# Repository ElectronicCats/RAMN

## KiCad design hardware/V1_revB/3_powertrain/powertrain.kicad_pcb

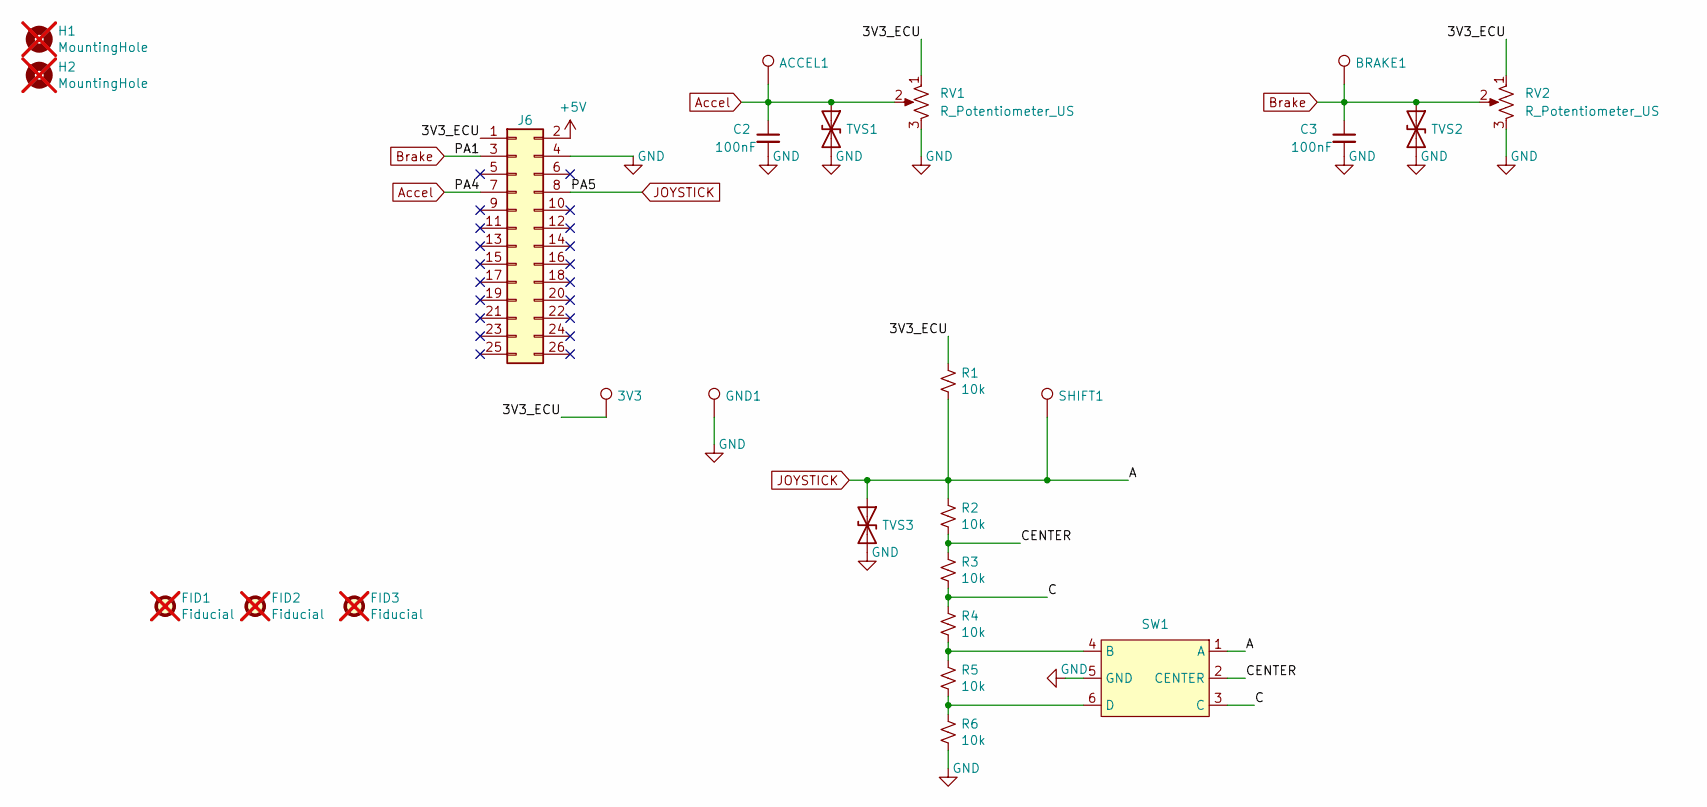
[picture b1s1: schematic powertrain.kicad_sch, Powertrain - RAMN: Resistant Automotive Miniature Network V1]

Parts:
3V3: TestPoint; KEYSTONE_5002; lcsc# C5277086
ACCEL1: TestPoint; KEYSTONE_5002; lcsc# C5277086
BRAKE1: TestPoint; KEYSTONE_5002; lcsc# C5277086
C2, C3: 100nF; C_0603_1608Metric; lcsc# C282519
FID1, FID2, FID3: Fiducial; Fiducial_1mm_Mask2mm; not fitted
GND1: TestPoint; KEYSTONE_5002; lcsc# C5277086
H1, H2: MountingHole; MountingHole_3.2mm_M3_ISO7380; not fitted
J6: PinSocket_2x13_P2.54mm_Vertical; lcsc# C2897414
R1, R2, R3, R4, R5, R6: 10k; R_0603_1608Metric; lcsc# C209220
RV1, RV2: R_Potentiometer_US; RS15111A900B; lcsc# C470417
SHIFT1: TestPoint; KEYSTONE_5002; lcsc# C5277086
SW1: SKRHADE010; lcsc# C202415
TVS1, TVS2, TVS3: D_TVS; D_SOD-123F; lcsc# C1849694

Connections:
+5V: J6.2
/3V3_ECU: 3V3.1 (1_1), J6.1, R1.1, RV1.1, RV2.1
/C: R3.2, R4.1, SW1.3 (C)
/CENTER: R2.2, R3.1, SW1.2 (CENTER)
Accel: ACCEL1.1 (1_1), C2.1, J6.7, RV1.2, TVS1.1 (A1)
Brake: BRAKE1.1 (1_1), C3.1, J6.3, RV2.2, TVS2.1 (A1)
GND: C2.2, C3.2, GND1.1 (1_1), J6.4, R6.2, RV1.3, RV2.3, SW1.5 (GND), TVS1.2 (A2), TVS2.2 (A2), TVS3.2 (A2)
JOYSTICK: J6.8, R1.2, R2.1, SHIFT1.1 (1_1), SW1.1 (A), TVS3.1 (A1)
unnamed: R4.2, R5.1, SW1.4 (B)
unnamed: R5.2, R6.1, SW1.6 (D)

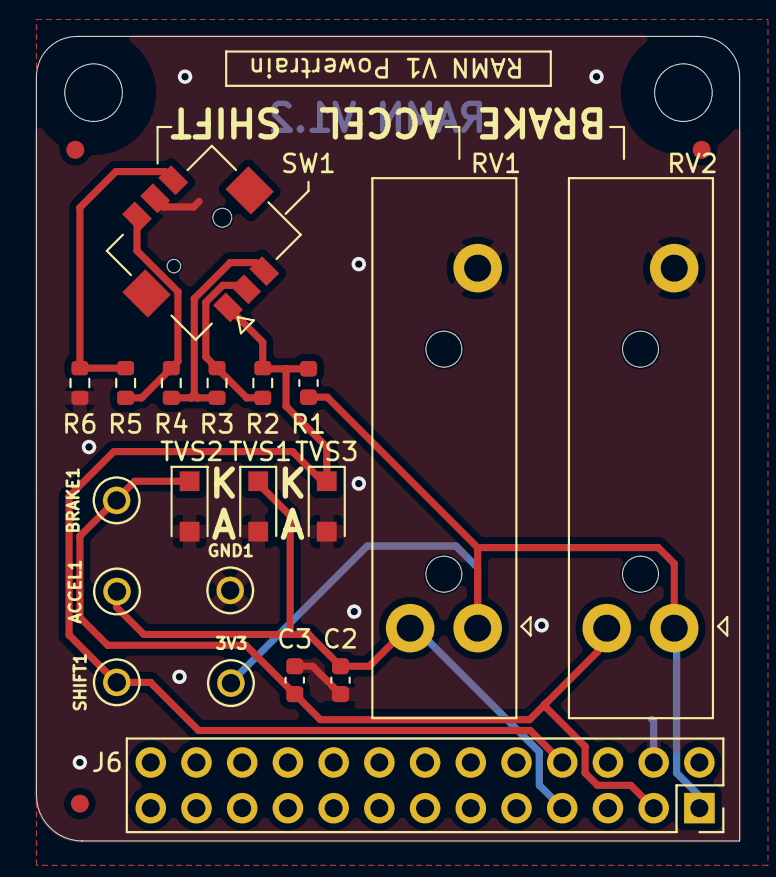
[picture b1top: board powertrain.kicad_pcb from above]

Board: 2 copper layers, 39.1 x 44.7 mm, 25 parts (0 on the bottom side), 9 nets.

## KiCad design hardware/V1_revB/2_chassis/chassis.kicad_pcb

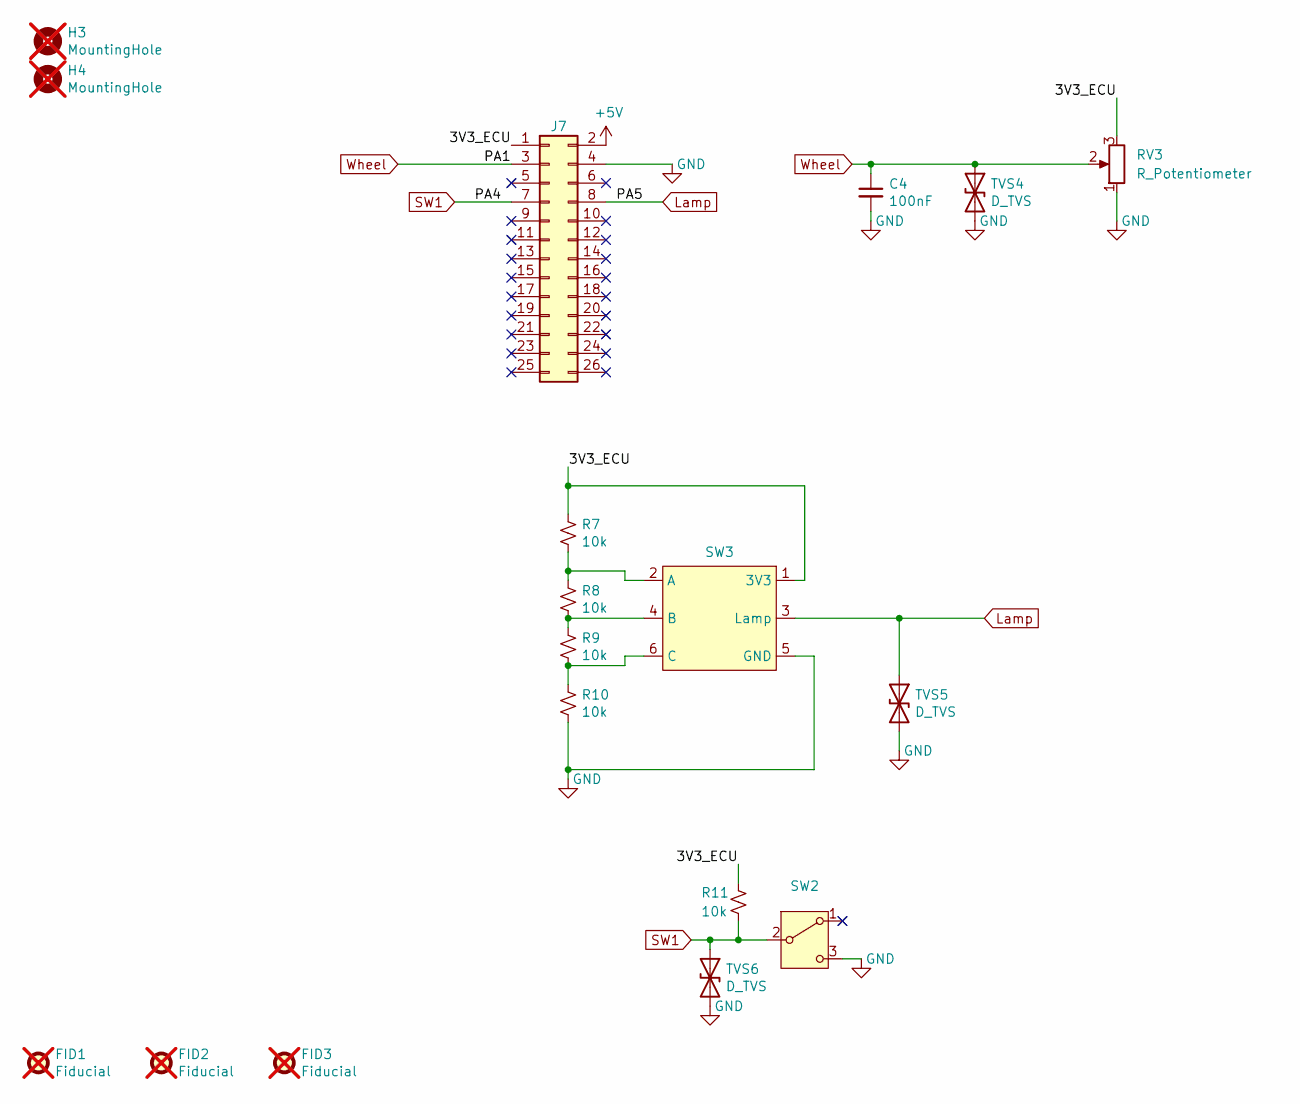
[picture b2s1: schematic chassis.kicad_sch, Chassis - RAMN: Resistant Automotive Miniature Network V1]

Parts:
C4: 100nF; C_0603_1608Metric; lcsc# C282519
FID1, FID2, FID3: Fiducial; Fiducial_1mm_Mask2mm; not fitted
H3, H4: MountingHole; MountingHole_3.2mm_M3_ISO7380; not fitted
J7: PinSocket_2x13_P2.54mm_Vertical; lcsc# C2897414
R7, R8, R9, R10, R11: 10k; R_0603_1608Metric; lcsc# C73809
RV3: R_Potentiometer; New_Pot; lcsc# C6139964
SW2: SW_CuK_OS102011MA1QN1_SPDT_Angled; lcsc# C226259
SW3: NR01; lcsc# C7250022
TVS4, TVS5, TVS6: D_TVS; D_SOD-123F; lcsc# C1849694

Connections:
+5V: J7.2
/3V3_ECU: J7.1, R7.1, R11.2, RV3.3, SW3.1 (3V3)
GND: C4.2, J7.4, R10.2, RV3.1, SW2.3 (C), SW3.5 (GND), TVS4.2 (A2), TVS5.2 (A2), TVS6.2 (A2)
Lamp: J7.8, SW3.3 (Lamp), TVS5.1 (A1)
unnamed: R7.2, R8.1, SW3.2 (A)
unnamed: R8.2, R9.1, SW3.4 (B)
unnamed: R9.2, R10.1, SW3.6 (C)
SW1: J7.7, R11.1, SW2.2 (B), TVS6.1 (A1)
Wheel: C4.1, J7.3, RV3.2, TVS4.1 (A1)

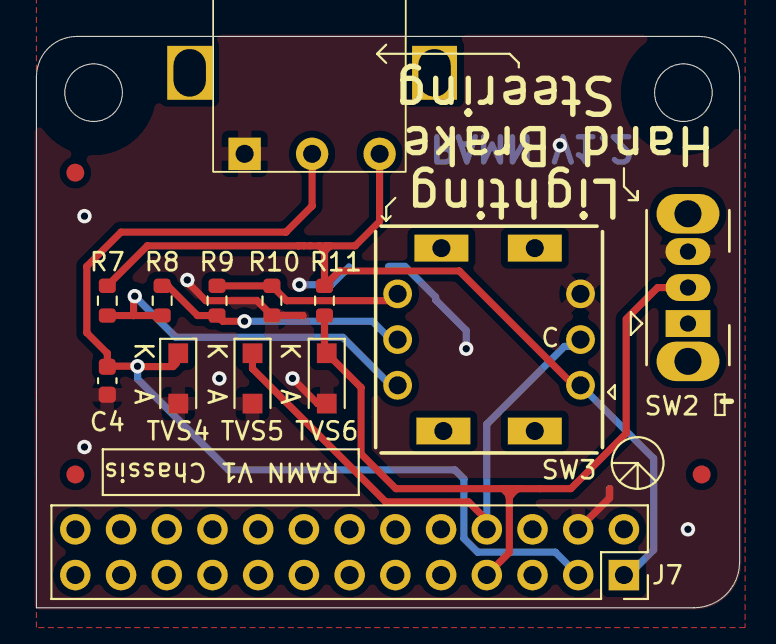
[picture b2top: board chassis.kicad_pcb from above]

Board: 2 copper layers, 39.1 x 31.7 mm, 18 parts (0 on the bottom side), 8 nets.

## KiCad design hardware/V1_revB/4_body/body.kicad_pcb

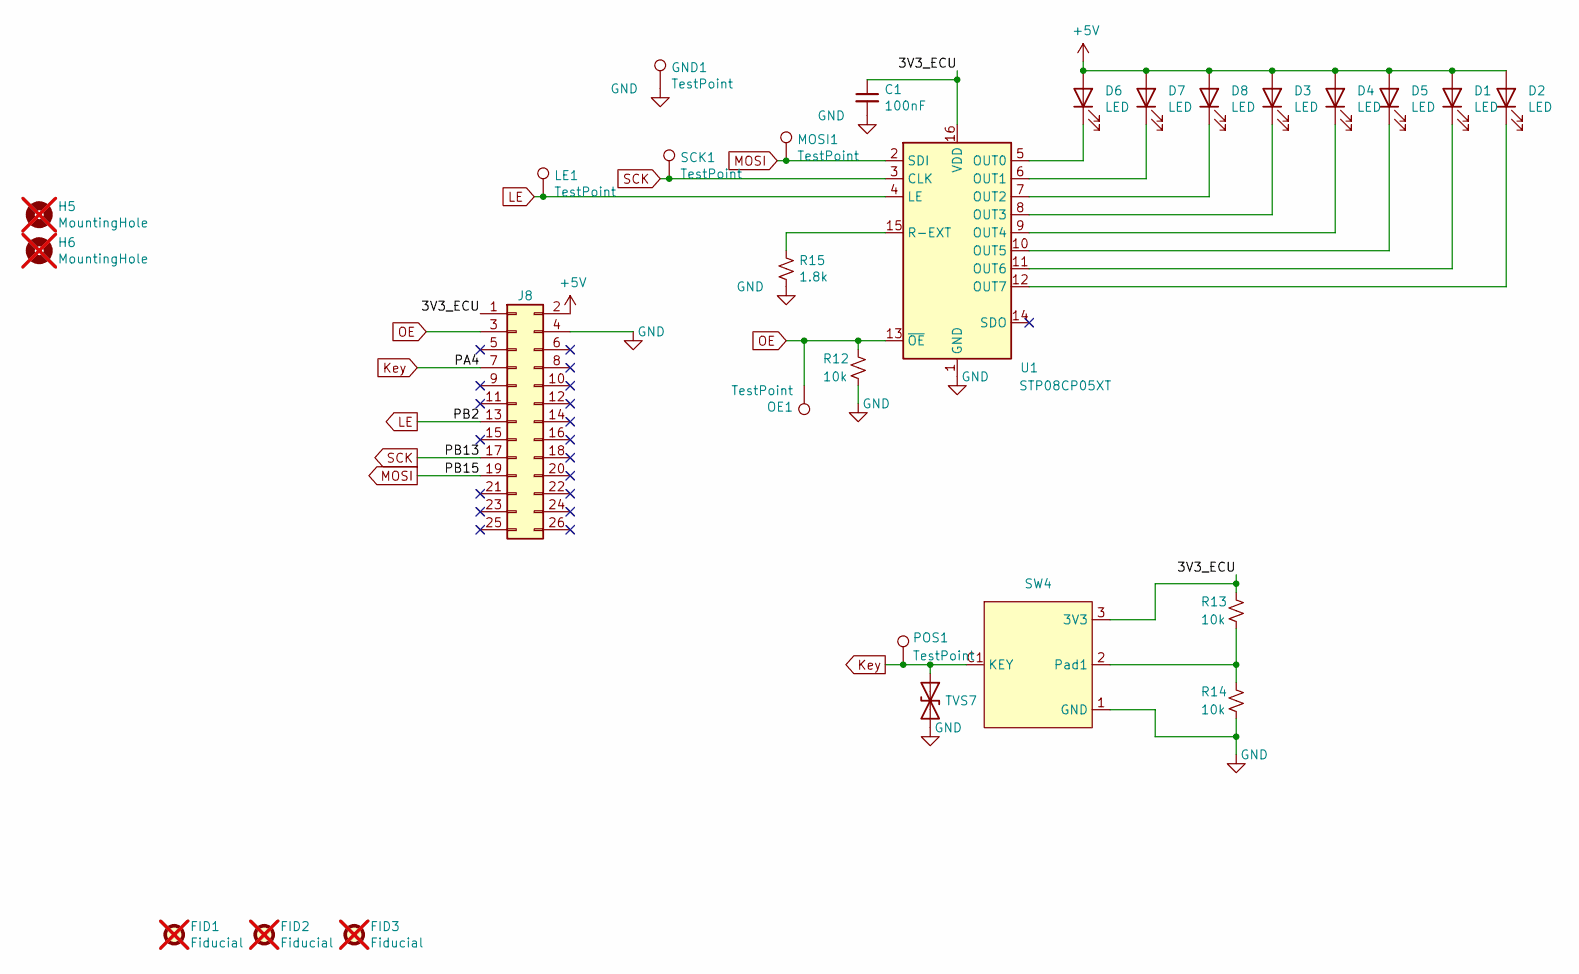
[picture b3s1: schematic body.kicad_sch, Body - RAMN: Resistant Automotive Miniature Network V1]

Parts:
C1: 100nF; C_0603_1608Metric; lcsc# C282519
D1, D2, D6: LED; LED_0603_1608Metric; lcsc# C51933295
D3, D4, D5: LED; LED_0603_1608Metric; lcsc# C510294
D7: LED; LED_0603_1608Metric; lcsc# C19273153
D8: LED; LED_0603_1608Metric; lcsc# C51933292
FID1, FID2, FID3: Fiducial; Fiducial_1mm_Mask2mm; not fitted
GND1: TestPoint; KEYSTONE_5002; lcsc# C5277086
H5, H6: MountingHole; MountingHole_3.2mm_M3_ISO7380; not fitted
J8: PinSocket_2x13_P2.54mm_Vertical; lcsc# C2897414
LE1: TestPoint; KEYSTONE_5002; lcsc# C5277086
MOSI1: TestPoint; KEYSTONE_5002; lcsc# C5277086
OE1: TestPoint; KEYSTONE_5002; lcsc# C5277086
POS1: TestPoint; KEYSTONE_5002; lcsc# C5277086
R12, R13, R14: 10k; R_0603_1608Metric; lcsc# C209220
R15: 1.8k; R_0603_1608Metric; lcsc# C171725
SCK1: TestPoint; KEYSTONE_5002; lcsc# C5277086
SW4: SK14dG13; lcsc# C34362858
TVS7: D_TVS; D_SOD-123F; lcsc# C1849694
U1: STP08CP05XT; HTSSOP-16-1EP_4.4x5mm_P0.65mm_EP3x3mm; lcsc# C2678539

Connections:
+5V: D1.2 (A), D2.2 (A), D3.2 (A), D4.2 (A), D5.2 (A), D6.2 (A), D7.2 (A), D8.2 (A), J8.2
/3V3_ECU: C1.1, J8.1, R13.2, SW4.3 (3V3), U1.16 (VDD)
GND: C1.2, GND1.1 (1_1), J8.4, R12.1, R14.1, R15.1, SW4.1 (GND), TVS7.2 (A2), U1.1 (GND), U1.17 (GND)
Key: J8.7, POS1.1 (1_1), SW4.C1 (KEY), TVS7.1 (A1)
LE: J8.13, LE1.1 (1_1), U1.4 (LE)
MOSI: J8.19, MOSI1.1 (1_1), U1.2 (SDI)
unnamed: D1.1 (K), U1.11 (OUT6)
unnamed: D2.1 (K), U1.12 (OUT7)
unnamed: D3.1 (K), U1.8 (OUT3)
unnamed: D4.1 (K), U1.9 (OUT4)
unnamed: D5.1 (K), U1.10 (OUT5)
unnamed: D6.1 (K), U1.5 (OUT0)
unnamed: D7.1 (K), U1.6 (OUT1)
unnamed: D8.1 (K), U1.7 (OUT2)
unnamed: R13.1, R14.2, SW4.2 (Pad1)
unnamed: R15.2, U1.15 (R-EXT)
OE: J8.3, OE1.1 (1_1), R12.2, U1.13 (~OE)
SCK: J8.17, SCK1.1 (1_1), U1.3 (CLK)

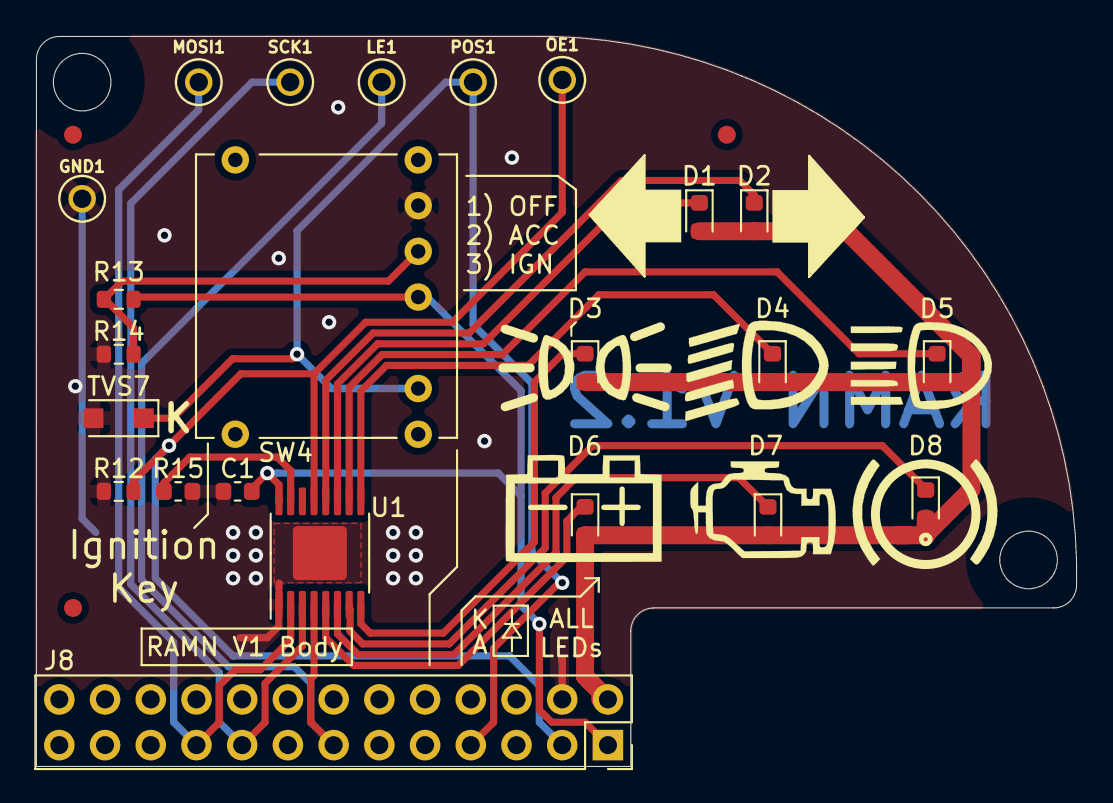
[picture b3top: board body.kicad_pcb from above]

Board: 2 copper layers, 57.8 x 40.6 mm, 28 parts (0 on the bottom side), 18 nets.

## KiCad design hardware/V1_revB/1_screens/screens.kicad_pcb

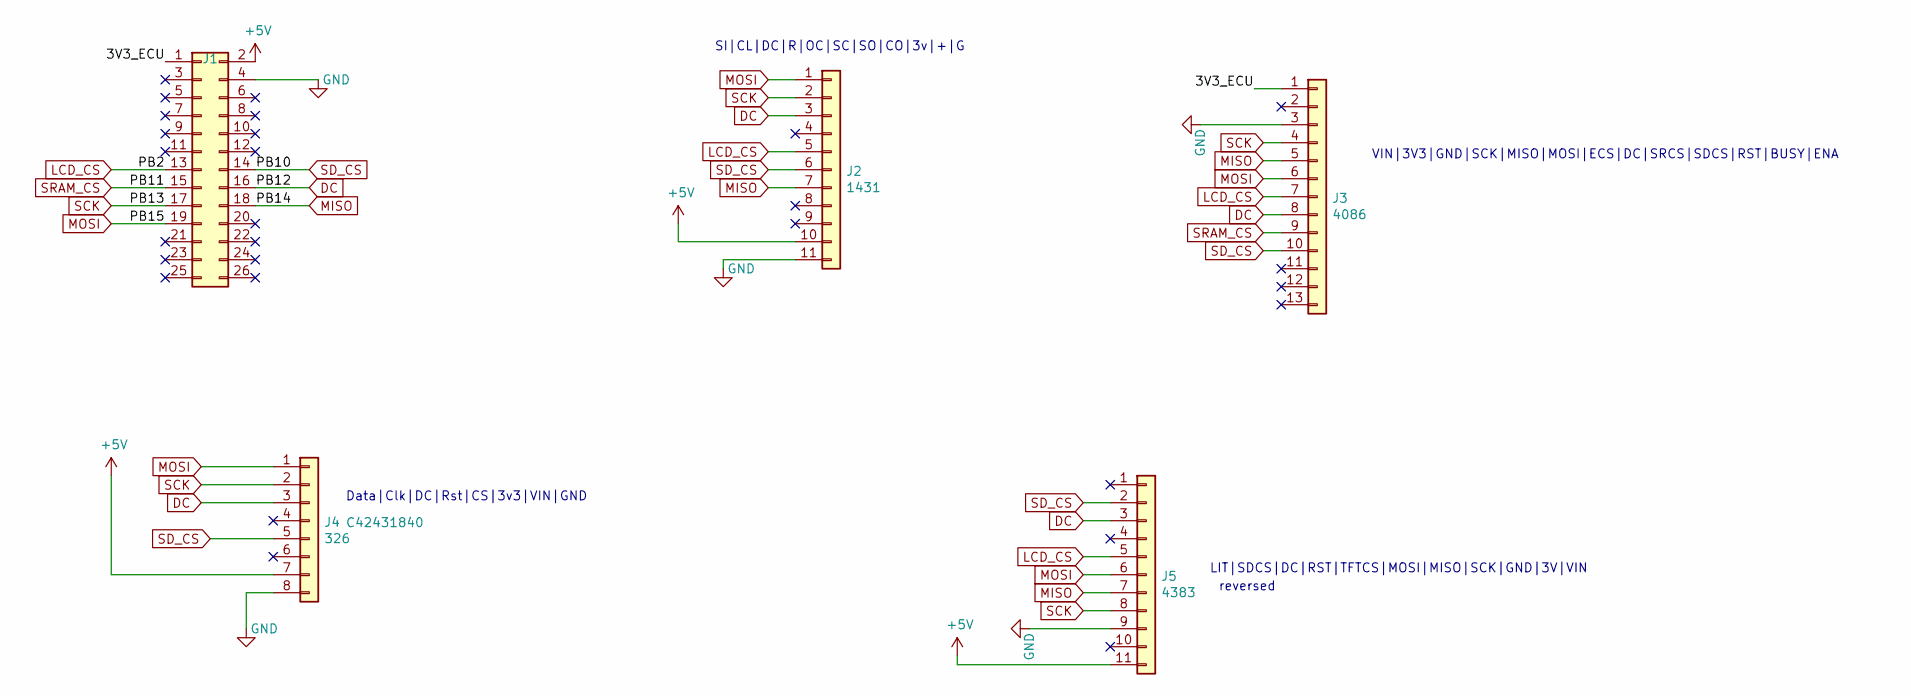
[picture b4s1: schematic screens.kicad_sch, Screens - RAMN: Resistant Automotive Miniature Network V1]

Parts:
J1: PinHeader_2x13_P2.54mm_Horizontal; LCSC C5412932
J2: 1431; PinSocket_1x11_P2.54mm_Vertical; LCSC C41417323
J3: 4086; PinSocket_1x13_P2.54mm_Vertical; LCSC C2905420
J4: 326; PinSocket_1x08_P2.54mm_Vertical; LCSC C42431840
J5: 4383; PinSocket_1x11_P2.54mm_Vertical; LCSC C41417323

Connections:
+5V: J1.2, J2.10, J4.7, J5.11
/3V3_ECU: J1.1, J3.1
DC: J1.16, J2.3, J3.8, J4.3, J5.3
GND: J1.4, J2.11, J3.3, J4.8, J5.9
LCD_CS: J1.13, J2.5, J3.7, J5.5
MISO: J1.18, J2.7, J3.5, J5.7
MOSI: J1.19, J2.1, J3.6, J4.1, J5.6
SCK: J1.17, J2.2, J3.4, J4.2, J5.8
SD_CS: J1.14, J2.6, J3.10, J4.5, J5.2
SRAM_CS: J1.15, J3.9

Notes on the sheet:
reversed
Data|Clk|DC|Rst|CS|3v3|VIN|GND
LIT|SDCS|DC|RST|TFTCS|MOSI|MISO|SCK|GND|3V|VIN
VIN|3V3|GND|SCK|MISO|MOSI|ECS|DC|SRCS|SDCS|RST|BUSY|ENA
SI|CL|DC|R|OC|SC|SO|CO|3v|+|G

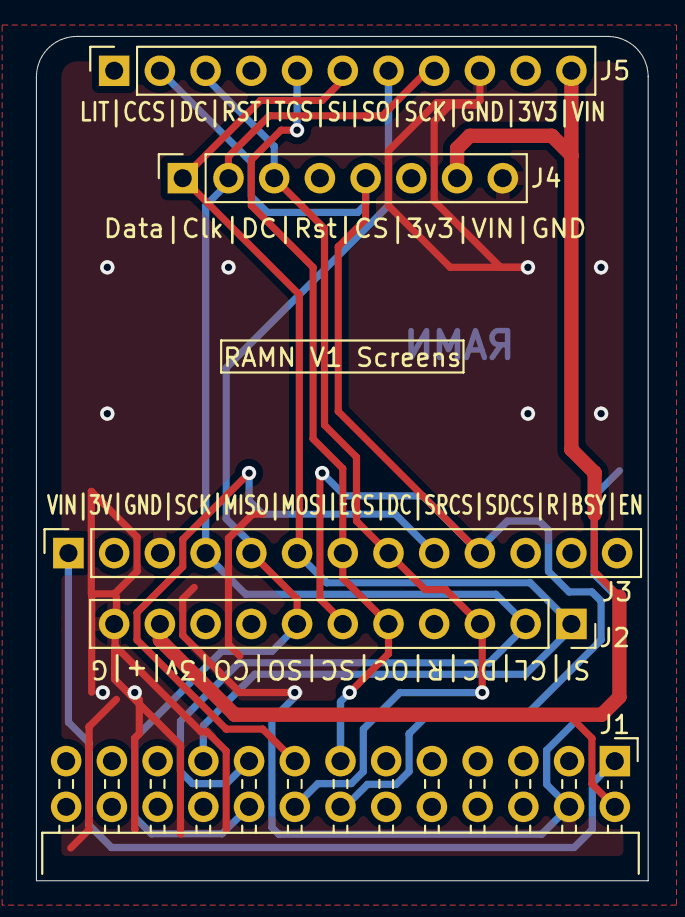
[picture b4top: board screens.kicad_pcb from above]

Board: 2 copper layers, 34.0 x 46.9 mm, 5 parts (0 on the bottom side), 10 nets.

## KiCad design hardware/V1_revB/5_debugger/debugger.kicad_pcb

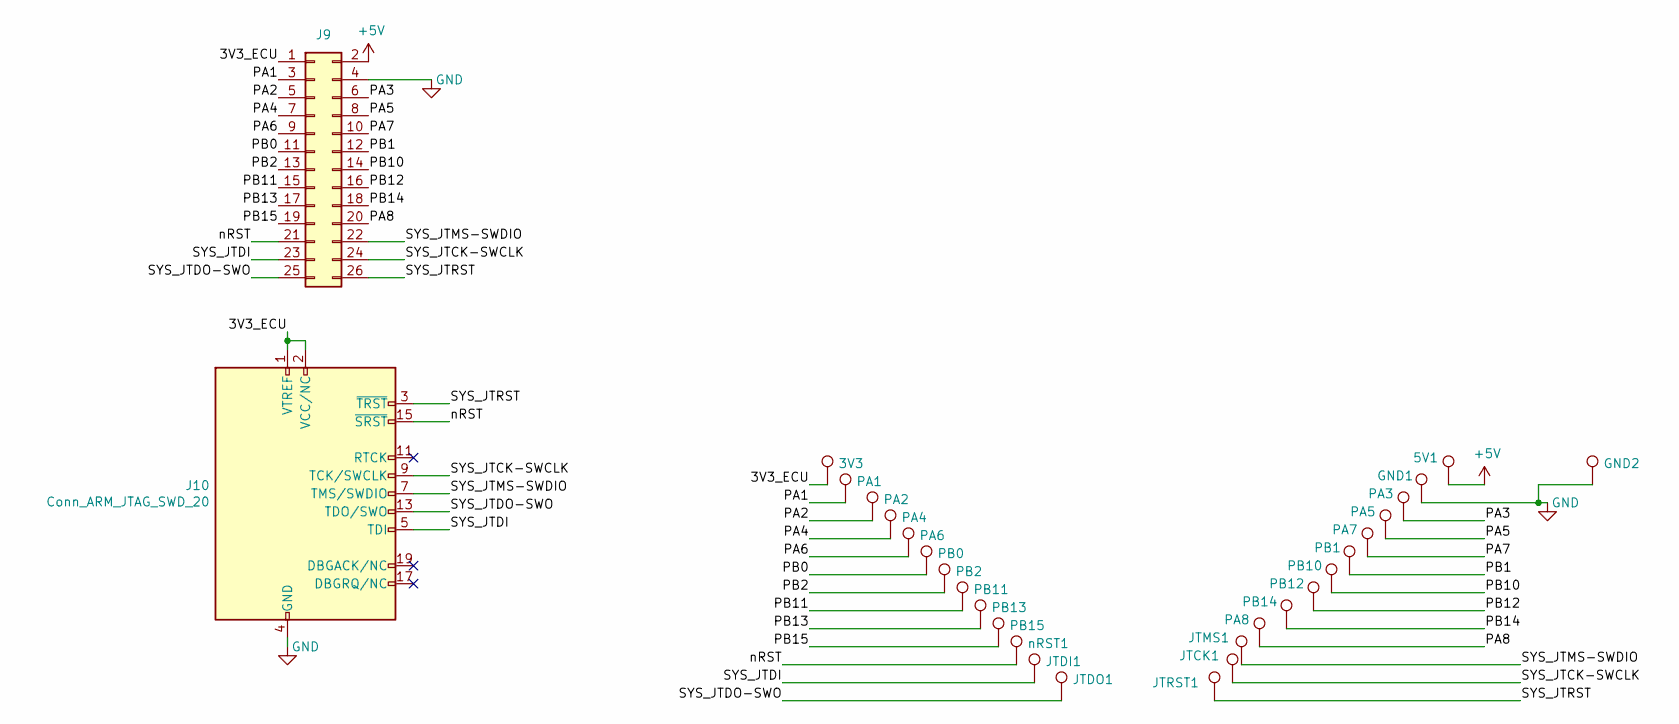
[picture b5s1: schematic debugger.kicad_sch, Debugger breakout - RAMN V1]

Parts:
3V3, 5V1: TestPoint; KEYSTONE_5002; lcsc# C5277086
GND1, GND2: TestPoint; KEYSTONE_5002; lcsc# C5277086
J9: PinSocket_2x13_P2.54mm_Vertical; lcsc# C2897414
J10: Conn_ARM_JTAG_SWD_20; IDC-Header_2x10_P2.54mm_Horizontal; lcsc# C7527716
JTCK1: TestPoint; KEYSTONE_5002; lcsc# C5277086
JTDI1: TestPoint; KEYSTONE_5002; lcsc# C5277086
JTDO1: TestPoint; KEYSTONE_5002; lcsc# C5277086
JTMS1: TestPoint; KEYSTONE_5002; lcsc# C5277086
JTRST1: TestPoint; KEYSTONE_5002; lcsc# C5277086
PA1, PA2, PA3, PA4, PA5, PA6, PA7, PA8: TestPoint; KEYSTONE_5002; lcsc# C5277086
PB0, PB1, PB2, PB10, PB11, PB12, PB13, PB14, PB15: TestPoint; KEYSTONE_5002; lcsc# C5277086
nRST1: TestPoint; KEYSTONE_5002; lcsc# C5277086

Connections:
+5V: 5V1.1 (1_1), J9.2
/3V3_ECU: 3V3.1 (1_1), J9.1, J10.1 (VTREF), J10.2 (VCC/NC)
/PA1: J9.3, PA1.1 (1_1)
/PA2: J9.5, PA2.1 (1_1)
/PA3: J9.6, PA3.1 (1_1)
/PA4: J9.7, PA4.1 (1_1)
/PA5: J9.8, PA5.1 (1_1)
/PA6: J9.9, PA6.1 (1_1)
/PA7: J9.10, PA7.1 (1_1)
/PA8: J9.20, PA8.1 (1_1)
/PB0: J9.11, PB0.1 (1_1)
/PB1: J9.12, PB1.1 (1_1)
/PB2: J9.13, PB2.1 (1_1)
/PB10: J9.14, PB10.1 (1_1)
/PB11: J9.15, PB11.1 (1_1)
/PB12: J9.16, PB12.1 (1_1)
/PB13: J9.17, PB13.1 (1_1)
/PB14: J9.18, PB14.1 (1_1)
/PB15: J9.19, PB15.1 (1_1)
/SYS_JTCK-SWCLK: J9.24, J10.9 (TCK/SWCLK), JTCK1.1 (1_1)
/SYS_JTDI: J9.23, J10.5 (TDI), JTDI1.1 (1_1)
/SYS_JTDO-SWO: J9.25, J10.13 (TDO/SWO), JTDO1.1 (1_1)
/SYS_JTMS-SWDIO: J9.22, J10.7 (TMS/SWDIO), JTMS1.1 (1_1)
/SYS_JTRST: J9.26, J10.3 (~TRST), JTRST1.1 (1_1)
/nRST: J9.21, J10.15 (~SRST), nRST1.1 (1_1)
GND: GND1.1 (1_1), GND2.1 (1_1), J9.4, J10.4 (GND), J10.6 (GND), J10.8 (GND), J10.10 (GND), J10.12 (GND), J10.14 (GND), J10.16 (GND), J10.18 (GND), J10.20 (GND)

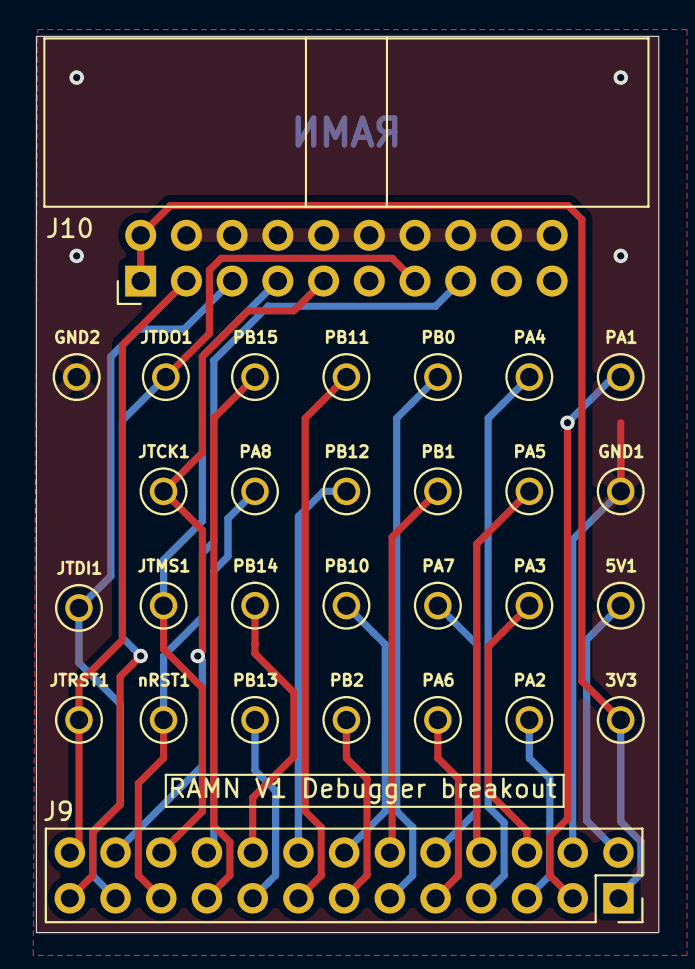
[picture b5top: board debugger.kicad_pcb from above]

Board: 2 copper layers, 34.6 x 49.8 mm, 29 parts (0 on the bottom side), 26 nets.

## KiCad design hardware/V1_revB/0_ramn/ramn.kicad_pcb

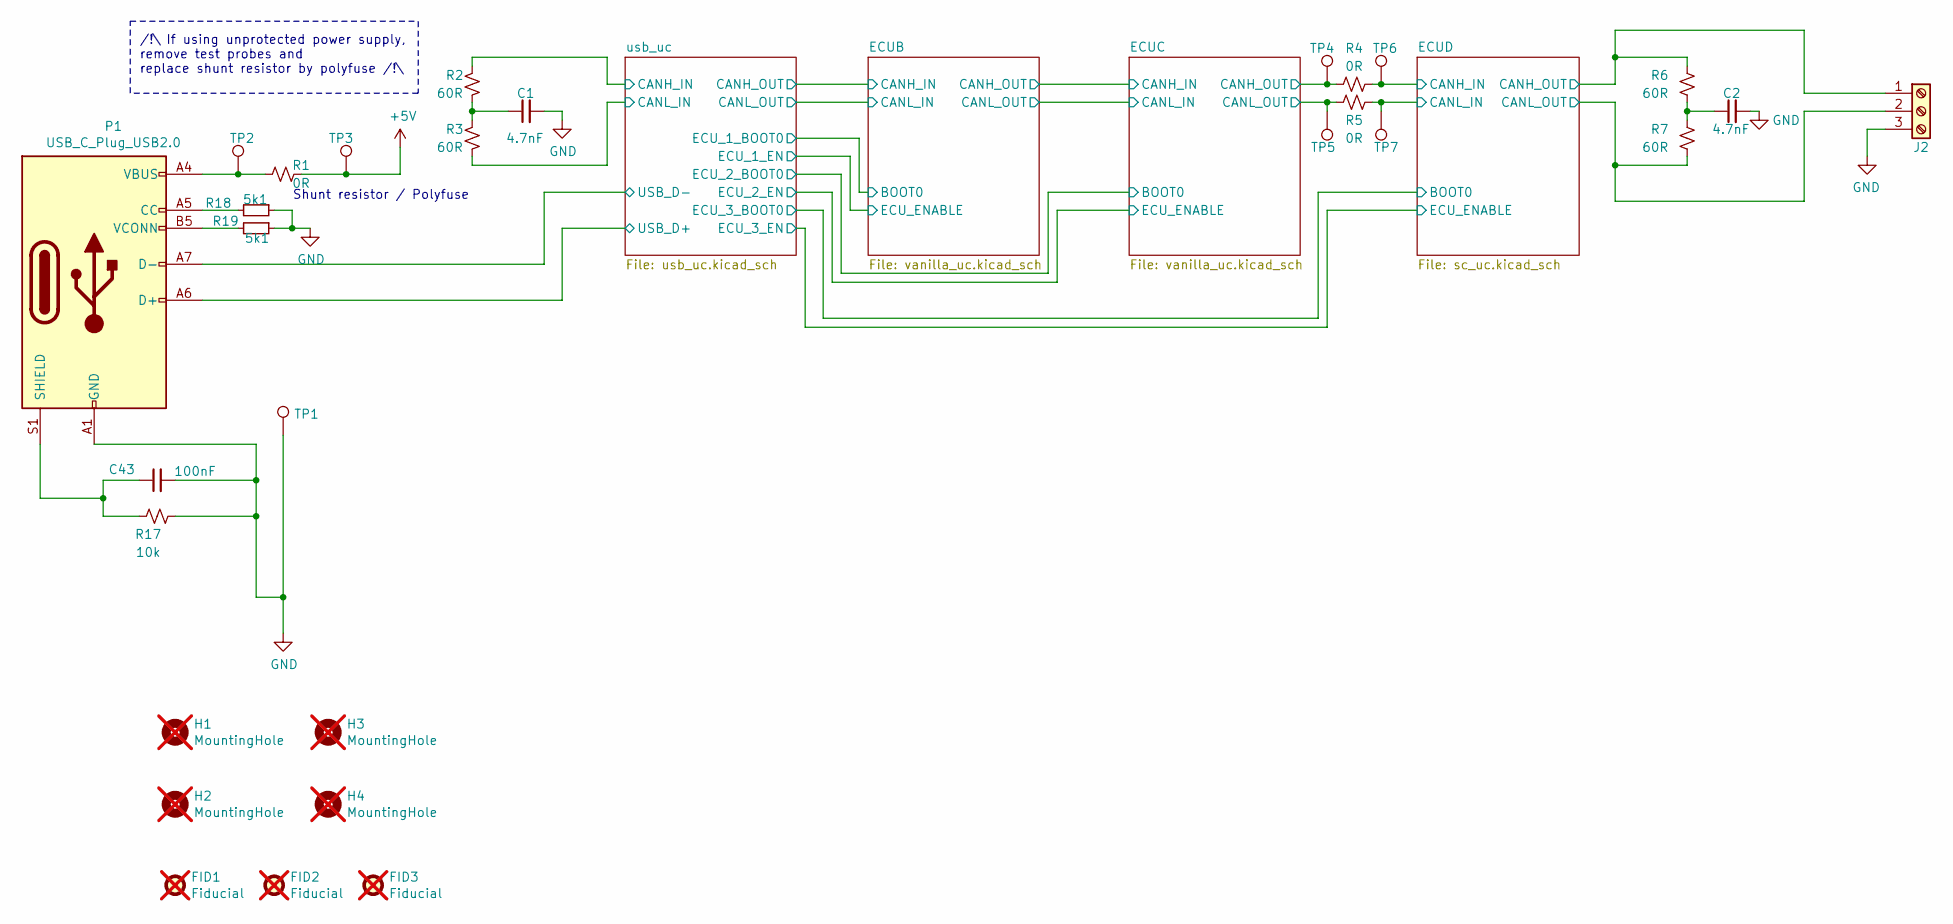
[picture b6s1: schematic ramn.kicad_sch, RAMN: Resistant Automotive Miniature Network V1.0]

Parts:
C1, C2: 4.7nF; C_0603_1608Metric; lcsc# C335546
C43: 100nF; C_0603_1608Metric; lcsc# C599645
FID1, FID2, FID3: Fiducial; Fiducial_1mm_Mask2mm; not fitted
H1, H2, H3, H4: MountingHole; MountingHole_3.2mm_M3_ISO7380; not fitted
J2: Screw_Terminal_01x03; TerminalBlock_Phoenix_PTSM-0,5-3-2.5-V-THR_1x03_P2.50mm_Ver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; lcsc# C5443579
P1: USB_C_Plug_USB2.0; C393939; lcsc# C393939
R1, R4, R5: 0R; R_0603_1608Metric; lcsc# C95177
R2, R3, R6, R7: 60R; R_0603_1608Metric; lcsc# C23090
R17: 10k; R_0603_1608Metric; lcsc# C98220
R18, R19: 5k1; R_0603_1608Metric; lcsc# C191782
TP1, TP2, TP3, TP4, TP5, TP6, TP7: KEYSTONE_5002; lcsc# C5277086

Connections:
+5V: R1.1, TP3.1 (1_1); also elsewhere on the board
/ECUB/CANH_IN: R2.1, R4.2, TP4.1 (1_1); also elsewhere on the board
/ECUB/CANL_IN: R3.2, R5.2, TP5.1 (1_1); also elsewhere on the board
/ECUD/CANH_IN: J2.1, R4.1, R6.1, TP6.1 (1_1); also elsewhere on the board
/ECUD/CANL_IN: J2.2, R5.1, R7.2, TP7.1 (1_1); also elsewhere on the board
/usb_uc/USB_D+: P1.A6 (D+); also elsewhere on the board
/usb_uc/USB_D-: P1.A7 (D-); also elsewhere on the board
GND: C1.2, C2.2, C43.2, J2.3, P1.A1 (GND), P1.A12 (GND), P1.B1 (GND), P1.B12 (GND), R17.2, R18.1, R19.1, TP1.1 (1_1); also elsewhere on the board
unnamed: C1.1, R2.2, R3.1
unnamed: C2.1, R6.2, R7.1
unnamed: P1.A5 (CC), R18.2
unnamed: C43.1, P1.S1 (SHIELD), R17.1
unnamed: P1.A4 (VBUS), P1.A9 (VBUS), P1.B4 (VBUS), P1.B9 (VBUS), R1.2, TP2.1 (1_1)
unnamed: P1.B5 (VCONN), R19.2

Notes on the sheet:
/!\ If using unprotected power supply, remove test probes and replace shunt resistor by polyfuse /!\
Shunt resistor / Polyfuse

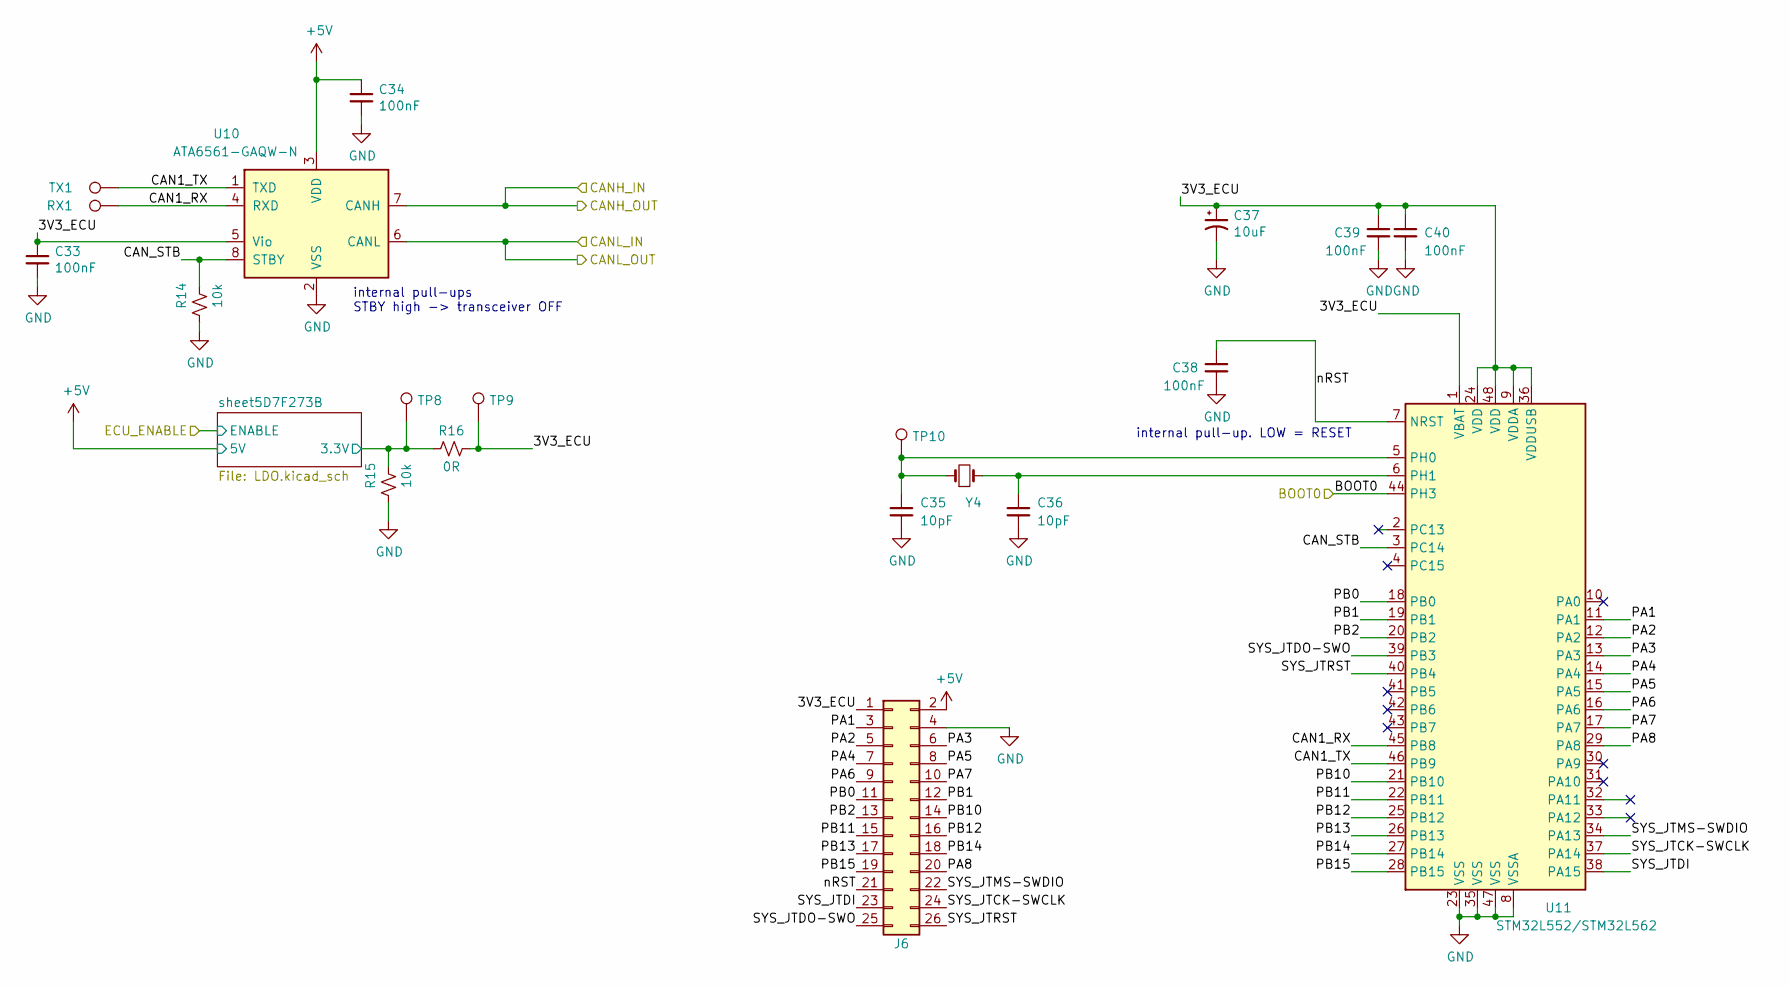
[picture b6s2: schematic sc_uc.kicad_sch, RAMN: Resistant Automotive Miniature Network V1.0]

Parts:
C33, C34, C38, C39, C40: 100nF; C_0603_1608Metric; lcsc# C599645
C35, C36: 10pF; C_0603_1608Metric; lcsc# C9807
C37: 10uF; C_1206_3216Metric; lcsc# C1848
J6: PinSocket_2x13_P2.54mm_Vertical; lcsc# C2897414
R14, R15: 10k; R_0603_1608Metric; lcsc# C98220
R16: 0R; R_0603_1608Metric; lcsc# C95177
RX1: TestPoint_Pad_D1.0mm; lcsc# C5277086
TP8, TP9, TP10: KEYSTONE_5002; lcsc# C5277086
TX1: TestPoint_Pad_D1.0mm; lcsc# C5277086
U10: ATA6561-GAQW-N; SOIC-8_3.9x4.9mm_P1.27mm; lcsc# C124015
U11: STM32L552/STM32L562; LQFP-48_7x7mm_P0.5mm; lcsc# C2969980
Y4: NX3225GD-8MHZ-STD-CRA-3; SMD-2_3.2x2.5mm; lcsc# C889706

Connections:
+5V: C34.1, J6.2, U10.3 (VDD); also elsewhere on the board
/ECUD/3V3_ECU: C33.1, C37.1, C39.1, C40.1, J6.1, R16.1, TP9.1 (1_1), U10.5 (Vio), U11.1 (VBAT), U11.9 (VDDA), U11.24 (VDD), U11.36 (VDDUSB), U11.48 (VDD)
/ECUD/BOOT0: U11.44 (PH3); also elsewhere on the board
/ECUD/CAN1_RX: RX1.1 (1_1), U10.4 (RXD), U11.45 (PB8)
/ECUD/CAN1_TX: TX1.1 (1_1), U10.1 (TXD), U11.46 (PB9)
/ECUD/CANH_IN: U10.7 (CANH); also elsewhere on the board
/ECUD/CANL_IN: U10.6 (CANL); also elsewhere on the board
/ECUD/CAN_STB: R14.1, U10.8 (STBY), U11.3 (PC14)
/ECUD/PA1: J6.3, U11.11 (PA1)
/ECUD/PA2: J6.5, U11.12 (PA2)
/ECUD/PA3: J6.6, U11.13 (PA3)
/ECUD/PA4: J6.7, U11.14 (PA4)
/ECUD/PA5: J6.8, U11.15 (PA5)
/ECUD/PA6: J6.9, U11.16 (PA6)
/ECUD/PA7: J6.10, U11.17 (PA7)
/ECUD/PA8: J6.20, U11.29 (PA8)
/ECUD/PB0: J6.11, U11.18 (PB0)
/ECUD/PB1: J6.12, U11.19 (PB1)
/ECUD/PB2: J6.13, U11.20 (PB2)
/ECUD/PB10: J6.14, U11.21 (PB10)
/ECUD/PB11: J6.15, U11.22 (PB11)
/ECUD/PB12: J6.16, U11.25 (PB12)
/ECUD/PB13: J6.17, U11.26 (PB13)
/ECUD/PB14: J6.18, U11.27 (PB14)
/ECUD/PB15: J6.19, U11.28 (PB15)
/ECUD/SYS_JTCK-SWCLK: J6.24, U11.37 (PA14)
/ECUD/SYS_JTDI: J6.23, U11.38 (PA15)
/ECUD/SYS_JTDO-SWO: J6.25, U11.39 (PB3)
/ECUD/SYS_JTMS-SWDIO: J6.22, U11.34 (PA13)
/ECUD/SYS_JTRST: J6.26, U11.40 (PB4)
/ECUD/nRST: C38.1, J6.21, U11.7 (NRST)
/ECUD/sheet5D7F273B/3.3V: R15.1, R16.2, TP8.1 (1_1); also elsewhere on the board
GND: C33.2, C34.2, C35.2, C36.2, C37.2, C38.2, C39.2, C40.2, J6.4, R14.2, R15.2, U10.2 (VSS), U11.8 (VSSA), U11.23 (VSS), U11.35 (VSS), U11.47 (VSS); also elsewhere on the board
unnamed: C35.1, TP10.1 (1_1), U11.5 (PH0), Y4.1
unnamed: C36.1, U11.6 (PH1), Y4.2

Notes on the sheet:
internal pull-up. LOW = RESET
internal pull-ups STBY high -> transceiver OFF

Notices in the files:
hardware/V1_revB/0_ramn/LDO.kicad_sch:
Copyright (c) 2024 TOYOTA MOTOR CORPORATION. ALL RIGHTS RESERVED.
License: CC BY-SA 4.0
hardware/V1_revB/1_screens/screens.kicad_sch:
Copyright (c) 2021 TOYOTA MOTOR CORPORATION. ALL RIGHTS RESERVED.
